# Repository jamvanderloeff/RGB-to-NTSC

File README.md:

# RGB-to-NTSC
 Converts RGB 15kHz video in the form of VGA or SCART into NTSC and/or PAL composite and s-video using

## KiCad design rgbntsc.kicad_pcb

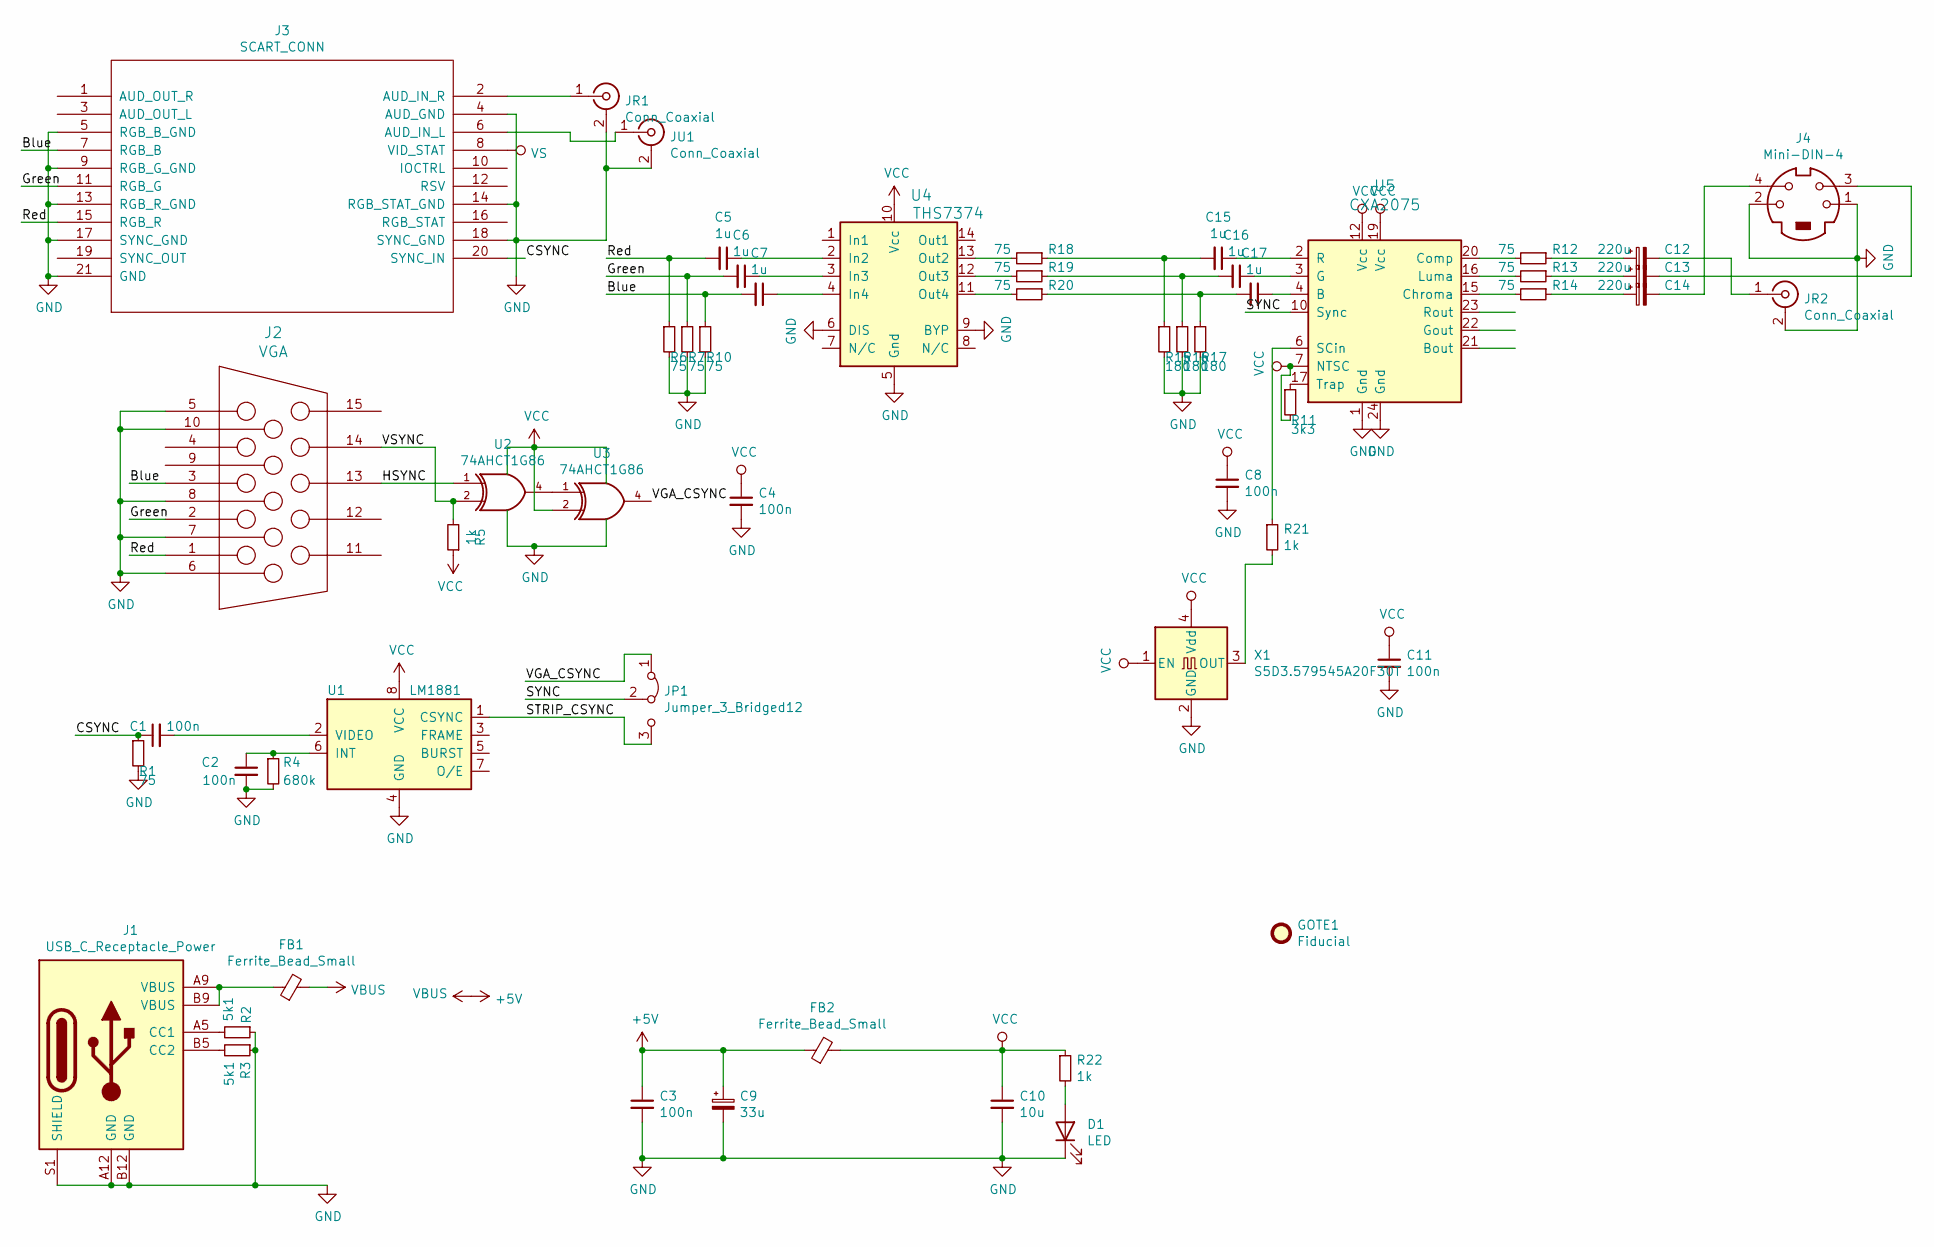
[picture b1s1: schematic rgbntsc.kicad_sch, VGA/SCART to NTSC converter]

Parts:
C1, C2, C3, C4, C8, C11: 100n; C_0805_2012Metric; LCSC C49678
C5, C6, C7, C15, C16, C17: 1u; C_0805_2012Metric; LCSC C28323
C9: 33u; CP_Elec_6.3x7.7; LCSC C127970
C10: 10u; C_0805_2012Metric; LCSC C15850
C12, C13, C14: 220u; CP_Elec_6.3x5.4; LCSC NOT FITTED
D1: LED; LED_0805_2012Metric; LCSC C34499
FB1, FB2: Ferrite_Bead_Small; C_0805_2012Metric; LCSC C1017
GOTE1: Fiducial; uwuriel; LCSC NOT FITTED
J1: USB_C_Receptacle_Power; USB_C_Receptacle_Generic_Power_Only; LCSC NOT FITTED
J2: VGA; VGA_CONN; LCSC NOT FITTED
J3: SCART_CONN; LCSC NOT FITTED
J4: Mini-DIN-4; CUI_MD-40SM; LCSC NOT FITTED
JP1: Jumper_3_Bridged12; SolderJumper-3_P1.3mm_Bridged12_Pad1.0x1.5mm; LCSC NOT FITTED
JR1, JR2: Conn_Coaxial; Cheapo_RCA_single_edge; LCSC NOT FITTED
JU1: Conn_Coaxial; Cheapo_RCA_single_edge; LCSC NOT FITTED
R1, R6, R7, R10, R12, R13, R14, R18, R19, R20: 75; R_0805_2012Metric; LCSC C20638
R2, R3: 5k1; R_0805_2012Metric; LCSC C27834
R4: 680k; R_0805_2012Metric; LCSC C17797
R5, R21, R22: 1k; R_0805_2012Metric; LCSC C17513
R11: 3k3; R_0805_2012Metric; LCSC C26010
R15, R16, R17: 180; R_0805_2012Metric; LCSC C25270
U1: LM1881; SOIC-8_3.9x4.9mm_P1.27mm; LCSC NOT FITTED
U2, U3: 74AHCT1G86; SOT-23-5; LCSC C43417
U4: THS7374; TSSOP-14_4.4x5mm_P0.65mm
U5: CXA2075; SO-24_5.3x15mm_P1.27mm; LCSC NOT FITTED
X1: S5D3.579545A20F30T; Oscillator_SMD_EuroQuartz_XO53-4Pin_5.0x3.2mm; LCSC C387187

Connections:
+5V: C3.1, C9.1, FB1.2, FB2.1
/Blue: C7.2, J2.3 (BLUE), J3.7 (RGB_B), R10.1
/CSYNC: C1.1, J3.20 (SYNC_IN), R1.1
/Green: C6.2, J2.2 (GREEN), J3.11 (RGB_G), R7.1
/HSYNC: J2.13 (HSYNC), U2.1
/Red: C5.2, J2.1 (RED), J3.15 (RGB_R), R6.1
/STRIP_CSYNC: JP1.3 (B), U1.1 (CSYNC)
/SYNC: JP1.2 (C), U5.10 (Sync)
/VGA_CSYNC: JP1.1 (A), U3.4
/VSYNC: J2.14 (VSYNC), R5.2, U2.2
GND: C2.2, C3.2, C4.2, C8.2, C9.2, C10.2, C11.2, D1.1 (K), J1.A12 (GND), J1.B12 (GND), J1.S1 (SHIELD), J2.5 (GND_HSYNC), J2.6 (RED_RTN), J2.7 (GREEN_RTN), J2.8 (BLUE_RTN), J2.10 (GND_VSYNC), J3.4 (AUD_GND), J3.5 (RGB_B_GND), J3.9 (RGB_G_GND), J3.13 (RGB_R_GND), J3.14 (RGB_STAT_GND), J3.17 (SYNC_GND), J3.18 (SYNC_GND), J3.21 (GND), J4.1, J4.2, JR1.2 (Ext), JR2.2 (Ext), JU1.2 (Ext), R1.2, R2.1, R3.1, R4.2, R6.2, R7.2, R10.2, R15.2, R16.2, R17.2, U1.4 (GND), U2.3 (GND), U3.3 (GND), U4.5 (Gnd), U4.6 (DIS), U4.9 (BYP), U5.1 (Gnd), U5.24 (Gnd), X1.2 (GND)
unnamed: C12.1, R12.1
unnamed: C13.1, R13.1
unnamed: C13.2, J4.3
unnamed: C14.1, R14.1
unnamed: C14.2, J4.4
unnamed: C15.2, R15.1, R18.1
unnamed: C16.2, R16.1, R19.1
unnamed: C17.2, R17.1, R20.1
unnamed: D1.2 (A), R22.2
unnamed: FB1.1, J1.A9 (VBUS), J1.B9 (VBUS)
unnamed: J1.A5 (CC1), R2.2
unnamed: J1.B5 (CC2), R3.2
unnamed: J3.6 (AUD_IN_L), JU1.1 (In)
unnamed: J3.2 (AUD_IN_R), JR1.1 (In)
unnamed: C12.2, JR2.1 (In)
unnamed: C2.1, R4.1, U1.6 (INT)
unnamed: C1.2, U1.2 (VIDEO)
unnamed: U2.4, U3.1
unnamed: C5.1, U4.2 (In2)
unnamed: C6.1, U4.3 (In3)
unnamed: C7.1, U4.4 (In4)
unnamed: R18.2, U4.13 (Out2)
unnamed: R19.2, U4.12 (Out3)
unnamed: R20.2, U4.11 (Out4)
unnamed: C17.1, U5.4 (B)
unnamed: R14.2, U5.15 (Chroma)
unnamed: R12.2, U5.20 (Comp)
unnamed: C16.1, U5.3 (G)
unnamed: R13.2, U5.16 (Luma)
unnamed: C15.1, U5.2 (R)
unnamed: R21.1, U5.6 (SCin)
unnamed: R11.1, U5.17 (Trap)
unnamed: R21.2, X1.3 (OUT)
VCC: C4.1, C8.1, C10.1, C11.1, FB2.2, R5.1, R11.2, R22.1, U1.8 (VCC), U2.5 (VCC), U3.2, U3.5 (VCC), U4.10 (Vcc), U5.7 (NTSC), U5.12 (Vcc), U5.19 (Vcc), X1.1 (EN), X1.4 (Vdd)
VS: J3.8 (VID_STAT)

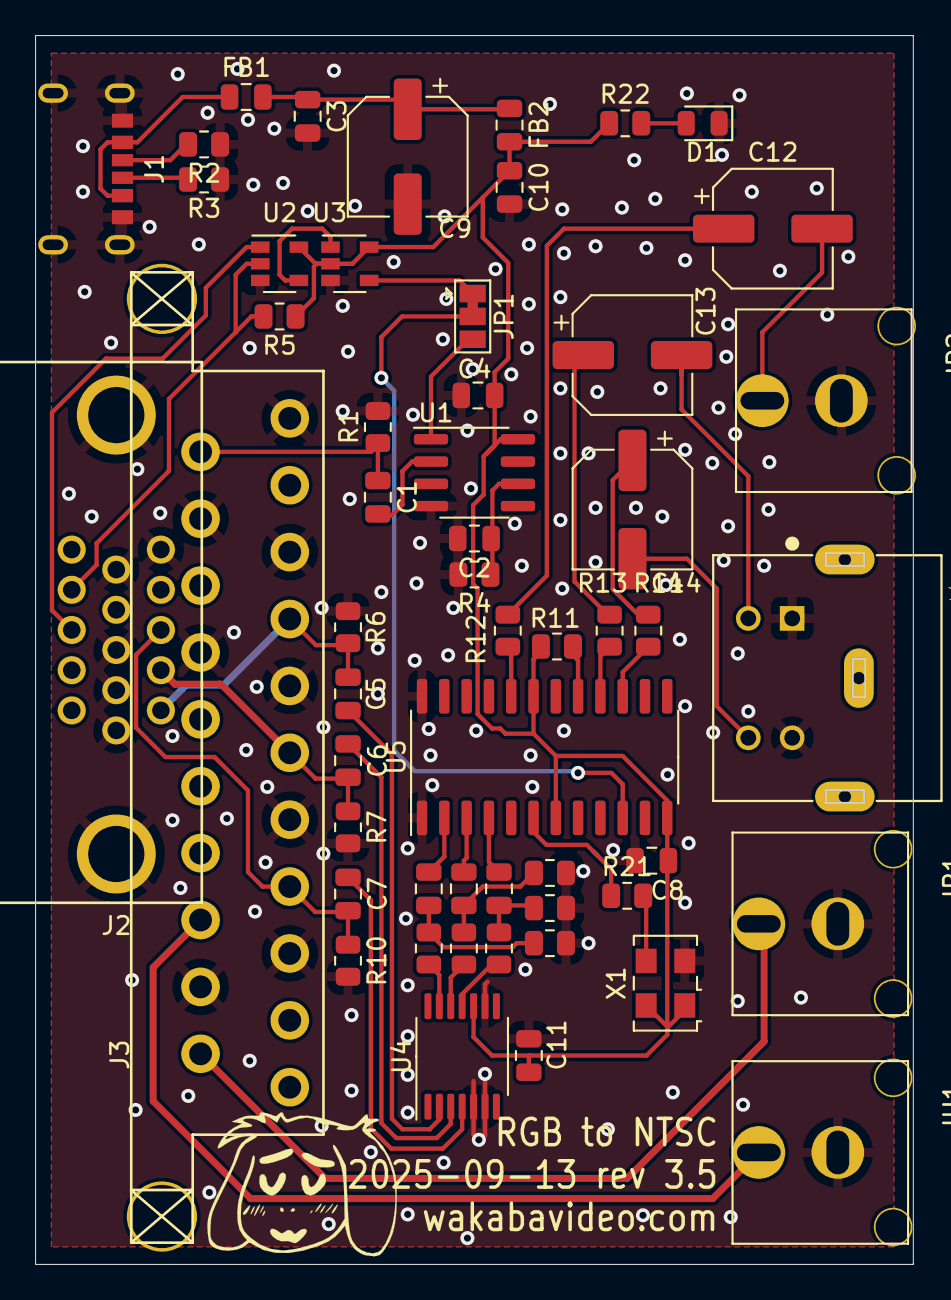
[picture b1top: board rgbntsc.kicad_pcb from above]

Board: 2 copper layers, 50.0 x 70.0 mm, 55 parts (0 on the bottom side), 45 nets.

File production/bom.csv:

Designator,Footprint,Quantity,Value,LCSC Part #
"C1, C11, C2, C3, C4, C8",0805,6,100n,C49678
C10,0805,1,10u,C15850
"C12, C13, C14",CP_Elec_6.3x5.4,3,220u,NOT FITTED
"C15, C16, C17, C5, C6, C7",0805,6,1u,C28323
C9,CP_Elec_6.3x7.7,1,33u,C127970
D1,0805,1,LED,C34499
"FB1, FB2",0805,2,Ferrite_Bead_Small,C1017
GOTE1,uwuriel,1,Fiducial,NOT FITTED
J1,USB_C_Receptacle_Generic_Power_Only,1,USB_C_Receptacle_Power,NOT FITTED
J2,VGA_CONN,1,VGA,NOT FITTED
J3,SCART_CONN,1,SCART_CONN,NOT FITTED
J4,CUI_MD-40SM,1,Mini-DIN-4,NOT FITTED
JP1,SolderJumper-3_P1.3mm_Bridged12_Pad1.0x1.5mm,1,Jumper_3_Bridged12,NOT FITTED
"JR1, JR2, JU1",Cheapo_RCA_single_edge,3,Conn_Coaxial,NOT FITTED
"R1, R10, R12, R13, R14, R18, R19, R20, R6, R7",0805,10,75,C17820
R11,0805,1,3k3,C26010
"R15, R16, R17",0805,3,180,C25270
"R2, R3",0805,2,5k1,C27834
"R21, R22, R5",0805,3,1k,C17513
R4,0805,1,680k,C17797
U1,SOIC-8_3.9x4.9mm_P1.27mm,1,LM1881,C518922
"U2, U3",SOT-23-5,2,74AHCT1G86,C43417
U4,TSSOP-14_4.4x5mm_P0.65mm,1,THS7374,C2652746
U5,SO-24_5.3x15mm_P1.27mm,1,CXA2075,NOT FITTED
X1,Oscillator_SMD_EuroQuartz_XO53-4Pin_5.0x3.2mm,1,S5D3.579545A20F30T,C2838127

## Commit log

2020-08-23 bit of cleanup and on github now woo
2020-08-23 cleanup and pdfs/gerbs
2020-10-19 update gerb
2020-11-21 CXA2075
    Replaces AD724 with CXA2075, also adds GBS compatible RGB out header
2020-12-19 added 1v amp and output caps
2020-12-28 corrected components
2021-06-18 add power LED, general tweakage
2021-07-08 fix regulator resistor, add schematic pdf
2021-09-23 add cover
2021-11-15 ditched supply reg, just filter harder
2021-11-15 new gerbs
2022-05-19 swapping parts
2022-09-16 updated gerbs, kicad 6 migration
2024-08-17 resync git i forgor what changed
2025-01-22 prod file updates
2025-10-04 cover prod files
2025-10-05 prod files for cover plates
